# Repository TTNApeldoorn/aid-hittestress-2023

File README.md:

# aid-hittestress-2023

These climate sensors are designed for the Homerus-Energiek project in Apeldoorn. They measures temperature, humidity and air quality.
The sensors are mounted in lampposts and communicate via LoRAWan with the TTN network.

## Requirements 
- The sensor measures each 2 minutes temperatue, humidity and particular matter PM1.0, 2.5 and 10
- The sensor sends the measurements to the TTN network using LoRaWan radio
- The sensor can be mounted on lamppost (case IP65)
- The sensor operates on LiPo battery (for minimal 18 hours) and can be charged by 230V supply 
- The sensor battery is charged at night by the lamppost
- GPS location and battery voltage are reported at regular intervals

## Realization

 Climate Sensor in Kradex housing

Air inlet dust sensor, with insect sreen

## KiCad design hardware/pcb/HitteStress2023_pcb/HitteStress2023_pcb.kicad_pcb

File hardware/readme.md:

# Homerus Klimaat sensor 2023
Notes on hardware for Homerus Klimaatsensor. 

## Hardware

Ik heb de software nu draaiend, met deepsleep en interne GPS,  met  SPS30 en AM2315 op de i2c.
De AM2315 en SPS30 zitten parallel op de I2C bus als volgt:
 pin 21 SDA
 pin 22 SCL
 AM2315 power op 3V3
 SDS30 power nu op de 5v pin, deze zakt naar 4v als het board op de batterij draait, dus volgens de specs net niet genoeg. Hiervoor moet dus een step-up naar 5v bij geplaatst worden.

Het board draait nu 24 uur op de batterij, en Vbat is van 4,095V nu gezakt naar 3,898V. Volgens mij houdt die het wel een tijdje uit op de batterij.

De 5v pin op het TTGO board is een 5v output pin, en geen 5v input. Dus de externe 5v voeding moet aangesloten worden op de micro USB connector, anders werkt het laad circuit niet.

https://github.com/Xinyuan-LilyGO/LilyGo-LoRa-Series

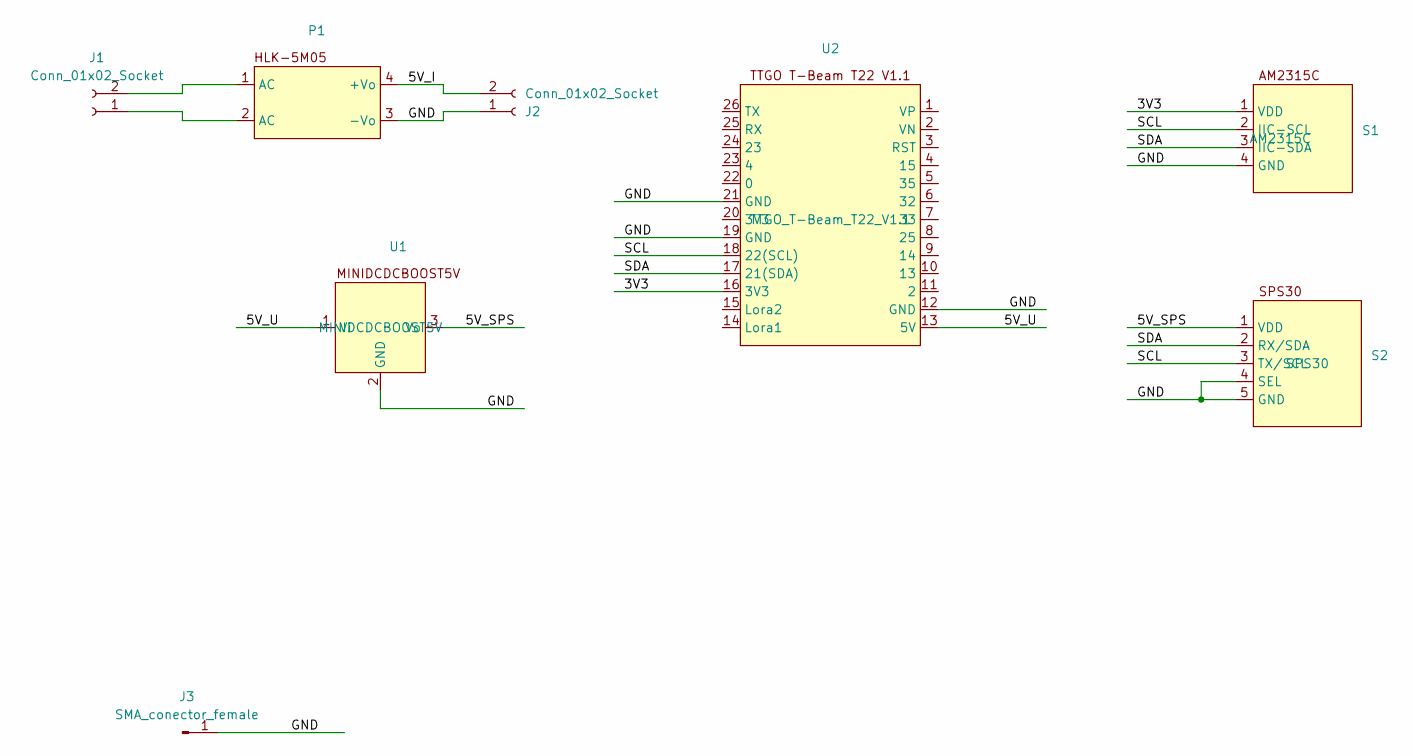
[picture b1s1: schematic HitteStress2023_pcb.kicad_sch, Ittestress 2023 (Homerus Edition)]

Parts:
J1: Conn_01x02_Socket; PhoenixContact_MCV_1,5_2-G-5.08_1x02_P5.08mm_Vertical
J2: Conn_01x02_Socket; TerminalBlock_Phoenix_MPT-0,5-2-2.54_1x02_P2.54mm_Horizontal
J3: SMA_conector_female; SMA-ANT-CONN
P1: HLK-5M05
S1: AM2315C
S2: SPS30
U1: MINIDCDCBOOST5V
U2: TTGO_T-Beam_T22_V1.1

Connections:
/3V3: S1.1 (VDD), U2.16 (3V3)
/5V_I: J2.2, P1.4 (+Vo)
/5V_SPS: S2.1 (VDD), U1.3 (Vo)
/5V_U: U1.1 (Vi), U2.13 (5V)
/GND: J2.1, J3.1, P1.3 (-Vo), S1.4 (GND), S2.4 (SEL), S2.5 (GND), U1.2 (GND), U2.12 (GND), U2.19 (GND), U2.21 (GND)
/SCL: S1.2 (IIC-SCL), S2.3 (TX/SCL), U2.18 (22(SCL))
/SDA: S1.3 (IIC-SDA), S2.2 (RX/SDA), U2.17 (21(SDA))
unnamed: J1.1, P1.2 (AC)
unnamed: J1.2, P1.1 (AC)

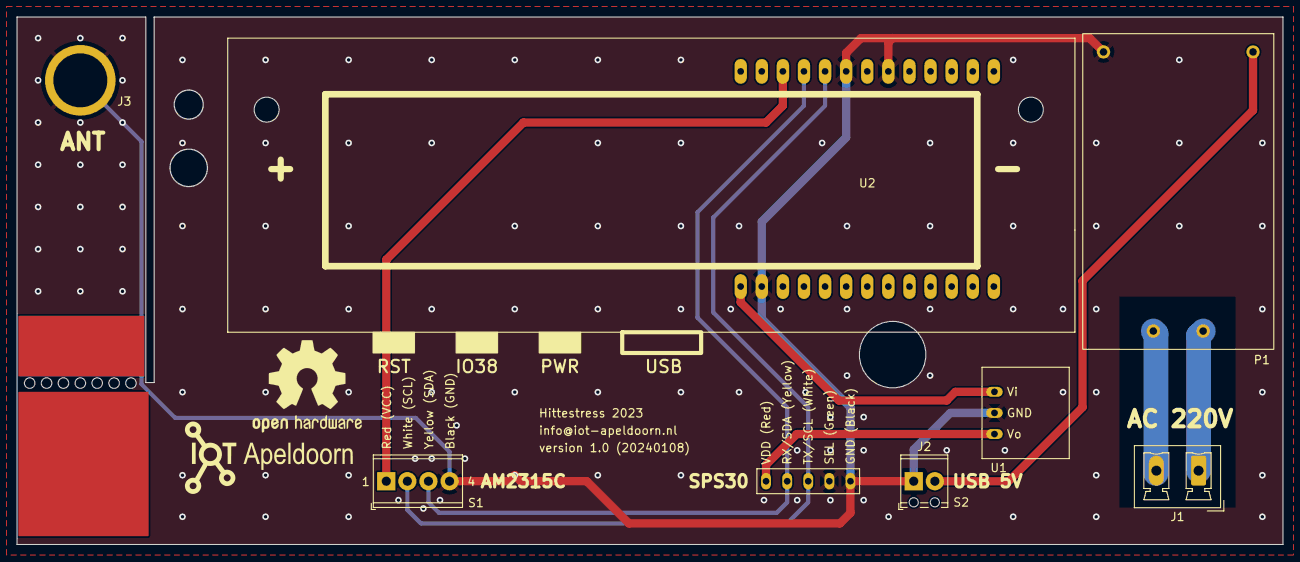
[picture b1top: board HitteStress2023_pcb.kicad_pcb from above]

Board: 2 copper layers, 152.4 x 63.4 mm, 8 parts (0 on the bottom side), 9 nets.

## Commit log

2023-12-18 Update, adding symbols
2023-12-20 Reorganization of libraries
2023-12-20 Started drawing
2023-12-20 Drawing progress, added mandatory component to BOM Hittestress Homerus 2023.xlsx
2023-12-21 Update drawing
2023-12-21 Added figure of TTGO T-Beam
2023-12-21 Finalised the day
2023-12-21 Update footprints
2023-12-21 Cleanup libraries
2023-12-22 Updated 3D representation
2023-12-22 Update design with IoT-Apeldoorn logo
2023-12-25 Updated PCB
2024-01-01 Verified and updated to v0.9 for first prototype print and ordered it.
2024-01-08 Version 1.0 after prototype soldering
2024-02-29 Add files via upload
    adapted for Visual Studio and LoRa libs changed to basicmac
2024-02-29 Update readme.md
    Adapted for Visual Studio and BasicMac lib
2024-03-11 Added drill plan for housing.
2025-07-18 Added 2x pull-pup resistors for I2C
